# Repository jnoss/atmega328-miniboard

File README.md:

# atmega328-miniboard
This is an atmega328 (arduino compatible) board that uses 3-pin headers (power and ground for each signal pin) enabling the use of very small shields.

See minishields directory for:
- led4pins.sch
- led8pins.sch
- light sensor microshield v3.sch
- rgb_v3.sch
- seg7_minishield.sch
- temp sensor.sch

See [gerber preview image](gerber-previews/mega328_withheaders_andxbee.brd.board-top.png) for a preview of the top layer of atmega328 miniboard

Board preview made using git hooks from [https://github.com/jnoss/eagle-preview-autogen], fork of [https://github.com/tekdemo/eagle-preview-autogen]

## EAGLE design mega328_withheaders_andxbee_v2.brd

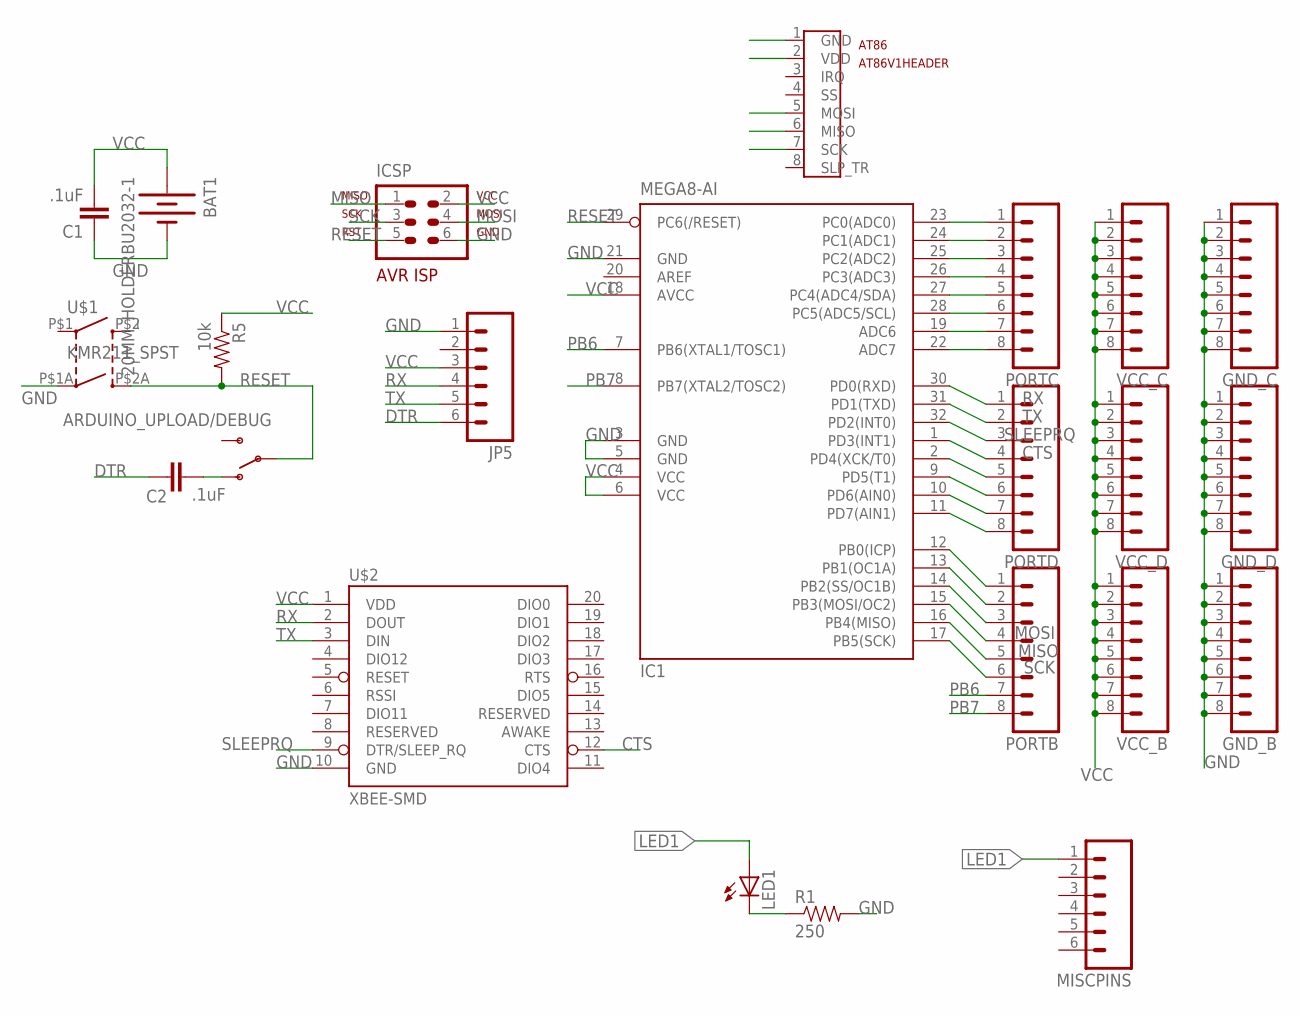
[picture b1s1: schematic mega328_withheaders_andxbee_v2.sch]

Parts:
ARDUINO_UPLOAD/DEBUG: SWITCH-SPDT-SMD-A; SWITCH-SPST-SMD-A
AT86: AT86V1HEADER
BAT1: 20MM_HOLDERBU2032-1; BU2032-1
C1, C2: .1uF; 0603-CAP
GND_B: M081X08; 1X08
GND_C: M081X08; 1X08
GND_D: M081X08; 1X08
IC1: MEGA8-AI; TQFP32-08
ICSP: ISP; AVR-ISP-6
JP5: M06SIP; 1X06
LED1: LEDCHIP-LED0603; CHIP-LED0603
MISCPINS: M06SIP; 1X06
PORTB: M081X08; 1X08
PORTC: M081X08; 1X08
PORTD: M081X08; 1X08
R1: 250; 0603-RES
R5: 10k; 0603-RES
U$1: KMR211_SPST
U$2: XBEE-SMD
VCC_B: M081X08; 1X08
VCC_C: M081X08; 1X08
VCC_D: M081X08; 1X08

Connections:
B0: IC1.12 (PB0(ICP)), PORTB.1
C0: IC1.23 (PC0(ADC0)), PORTC.1
CTS: IC1.1 (PD3(INT1)), PORTD.4, U$2.12 (CTS)
DTR: C2.1, JP5.6
GND: AT86.1 (GND), BAT1.-, C1.1, GND_B.1, GND_B.2, GND_B.3, GND_B.4, GND_B.5, GND_B.6, GND_B.7, GND_B.8, GND_C.1, GND_C.2, GND_C.3, GND_C.4, GND_C.5, GND_C.6, GND_C.7, GND_C.8, GND_D.1, GND_D.2, GND_D.3, GND_D.4, GND_D.5, GND_D.6, GND_D.7, GND_D.8, IC1.3 (GND), IC1.5 (GND), IC1.21 (GND), ICSP.6, JP5.1, R1.2, U$1.P$1A (1B), U$2.10 (GND)
LED1: LED1.A, MISCPINS.1
MISO: AT86.6 (MISO), IC1.16 (PB4(MISO)), ICSP.1, PORTB.5
MOSI: AT86.5 (MOSI), IC1.15 (PB3(MOSI/OC2)), ICSP.4, PORTB.4
unnamed: ARDUINO_UPLOAD/DEBUG.1 (O), C2.2
unnamed: IC1.24 (PC1(ADC1)), PORTC.2
unnamed: IC1.25 (PC2(ADC2)), PORTC.3
unnamed: IC1.26 (PC3(ADC3)), PORTC.4
unnamed: IC1.27 (PC4(ADC4/SDA)), PORTC.5
unnamed: IC1.28 (PC5(ADC5/SCL)), PORTC.6
unnamed: IC1.19 (ADC6), PORTC.7
unnamed: IC1.22 (ADC7), PORTC.8
unnamed: IC1.2 (PD4(XCK/T0)), PORTD.5
unnamed: IC1.9 (PD5(T1)), PORTD.6
unnamed: IC1.10 (PD6(AIN0)), PORTD.7
unnamed: IC1.11 (PD7(AIN1)), PORTD.8
unnamed: IC1.14 (PB2(SS/OC1B)), PORTB.3
unnamed: IC1.13 (PB1(OC1A)), PORTB.2
unnamed: LED1.C, R1.1
PB6: IC1.7 (PB6(XTAL1/TOSC1)), PORTB.7
PB7: IC1.8 (PB7(XTAL2/TOSC2)), PORTB.8
RESET: ARDUINO_UPLOAD/DEBUG.2, IC1.29 (PC6(/RESET)), ICSP.5, R5.2, U$1.P$2A (2B)
RX: IC1.30 (PD0(RXD)), JP5.4, PORTD.1, U$2.2 (DOUT)
SCK: AT86.7 (SCK), IC1.17 (PB5(SCK)), ICSP.3, PORTB.6
SLEEPRQ: IC1.32 (PD2(INT0)), PORTD.3, U$2.9 (DTR/SLEEP_RQ)
TX: IC1.31 (PD1(TXD)), JP5.5, PORTD.2, U$2.3 (DIN)
VCC: AT86.2 (VDD), BAT1.+@1 (+), BAT1.+@2 (+), C1.2, IC1.4 (VCC), IC1.6 (VCC), IC1.18 (AVCC), ICSP.2, JP5.3, R5.1, U$2.1 (VDD), VCC_B.1, VCC_B.2, VCC_B.3, VCC_B.4, VCC_B.5, VCC_B.6, VCC_B.7, VCC_B.8, VCC_C.1, VCC_C.2, VCC_C.3, VCC_C.4, VCC_C.5, VCC_C.6, VCC_C.7, VCC_C.8, VCC_D.1, VCC_D.2, VCC_D.3, VCC_D.4, VCC_D.5, VCC_D.6, VCC_D.7, VCC_D.8

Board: 2 copper layers, 23 parts (1 on the bottom side), 31 nets, no tracks yet.

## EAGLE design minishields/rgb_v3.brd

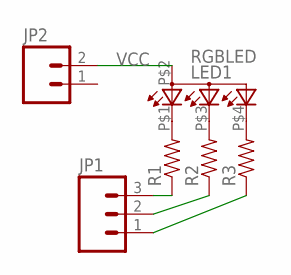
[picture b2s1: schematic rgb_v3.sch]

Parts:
JP1: M03NONPOLAR; 1X03NONPOLAR
JP2: M02PTH; 1X02
LED1: RGBLED; CLVBA-FKA-CAEDH8BBB7A363
R1, R2, R3: RESISTOR0402-RES; 0402-RES

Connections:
unnamed: LED1.P$1 (CRED), R1.2
unnamed: LED1.P$3 (CBLUE), R2.2
unnamed: LED1.P$4 (CGREEN), R3.2
unnamed: JP1.2, R2.1
unnamed: JP1.1, R3.1
unnamed: JP1.3, R1.1
VCC: JP2.2, LED1.P$2 (A)

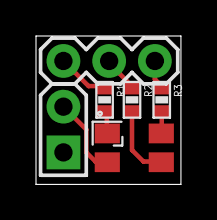
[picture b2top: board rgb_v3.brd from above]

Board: 2 copper layers, 8.1 x 8.2 mm, 6 parts (0 on the bottom side), 7 nets.

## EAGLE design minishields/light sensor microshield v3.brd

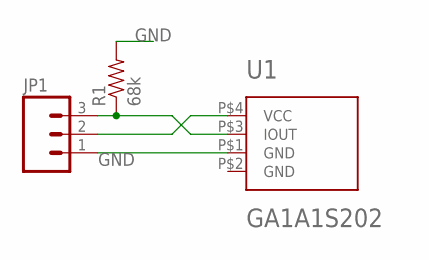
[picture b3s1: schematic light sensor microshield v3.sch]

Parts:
JP1: M03PTH; 1X03
R1: 68k; 0603-RES
U1: GA1A1S202; GA1A12S202

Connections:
GND: JP1.1, R1.2, U1.P$1 (GND), U1.P$2 (GND)
unnamed: JP1.2, U1.P$4 (VCC)
unnamed: JP1.3, R1.1, U1.P$3 (IOUT)

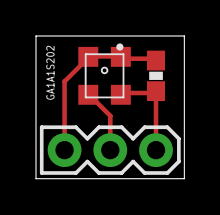
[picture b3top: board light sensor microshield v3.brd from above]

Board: 2 copper layers, 8.2 x 7.9 mm, 3 parts (0 on the bottom side), 3 nets.

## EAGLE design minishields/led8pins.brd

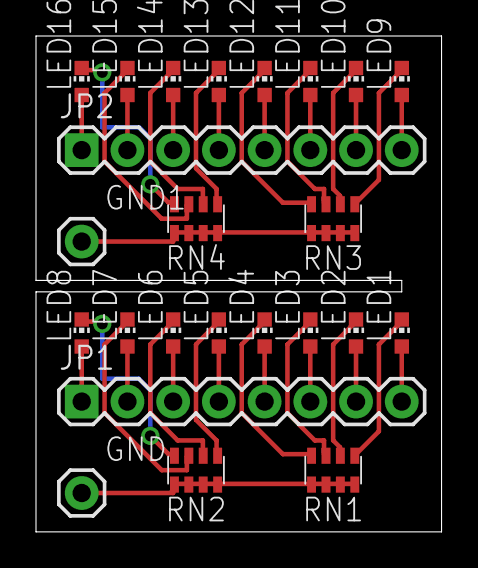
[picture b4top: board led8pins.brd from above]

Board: 2 copper layers, 22.5 x 27.5 mm, 24 parts (0 on the bottom side), 34 nets.

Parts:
GND, GND1: M01PTH; 1X01
JP1, JP2: 1X08
LED1, LED2, LED3, LED4, LED5, LED6, LED7, LED8, LED9, LED10, LED11, LED12, LED13, LED14, LED15, LED16: CHIP-LED0603
RN1, RN2, RN3, RN4: CTS742C083

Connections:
unnamed: JP1.8, LED1.A
unnamed: JP1.7, LED2.A
unnamed: JP1.6, LED3.A
unnamed: JP1.5, LED4.A
unnamed: JP1.4, LED5.A
unnamed: JP1.3, LED6.A
unnamed: JP1.2, LED7.A
unnamed: JP1.1, LED8.A
unnamed: LED1.C, RN1.1
unnamed: LED2.C, RN1.2
unnamed: LED3.C, RN1.3
unnamed: LED4.C, RN1.4
unnamed: LED5.C, RN2.1
unnamed: LED6.C, RN2.2
unnamed: LED7.C, RN2.3
unnamed: LED8.C, RN2.4
unnamed: GND.1, RN1.5, RN1.6, RN1.7, RN1.8, RN2.5, RN2.6, RN2.7, RN2.8
unnamed: JP2.8, LED9.A
unnamed: JP2.7, LED10.A
unnamed: JP2.6, LED11.A
unnamed: JP2.5, LED12.A
unnamed: JP2.4, LED13.A
unnamed: JP2.3, LED14.A
unnamed: JP2.2, LED15.A
unnamed: JP2.1, LED16.A
unnamed: LED9.C, RN3.1
unnamed: LED10.C, RN3.2
unnamed: LED11.C, RN3.3
unnamed: LED12.C, RN3.4
unnamed: LED13.C, RN4.1
unnamed: LED14.C, RN4.2
unnamed: LED15.C, RN4.3
unnamed: LED16.C, RN4.4
unnamed: GND1.1, RN3.5, RN3.6, RN3.7, RN3.8, RN4.5, RN4.6, RN4.7, RN4.8

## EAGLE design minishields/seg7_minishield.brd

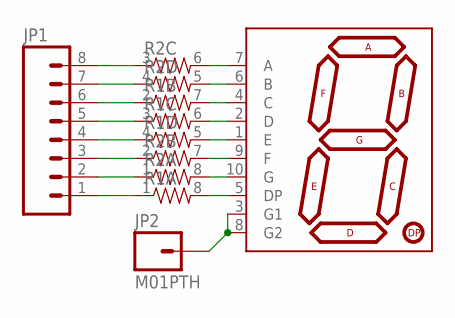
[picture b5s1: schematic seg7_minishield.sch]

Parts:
JP1: M081X08; 1X08
JP2: M01PTH; 1X01
R1, R2: RESISTOR-ARRAY0603-ARV; 0603-ARV
U$1: 7-SEGMENT-DISPLAYPTH; 7-SEGMENT-DISPLAY

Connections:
unnamed: R1.5 (2), U$1.1 (E)
unnamed: R1.6 (2), U$1.2 (D)
unnamed: R1.7 (2), U$1.4 (C)
unnamed: R1.8 (2), U$1.5 (DP)
unnamed: R2.8 (2), U$1.10 (G)
unnamed: R2.7 (2), U$1.9 (F)
unnamed: R2.6 (2), U$1.7 (A)
unnamed: R2.5 (2), U$1.6 (B)
unnamed: JP2.1, U$1.3 (G1), U$1.8 (G2)
unnamed: JP1.1, R1.1
unnamed: JP1.6, R1.2 (1)
unnamed: JP1.5, R1.3 (1)
unnamed: JP1.4, R1.4 (1)
unnamed: JP1.2, R2.1
unnamed: JP1.3, R2.2 (1)
unnamed: JP1.8, R2.3 (1)
unnamed: JP1.7, R2.4 (1)

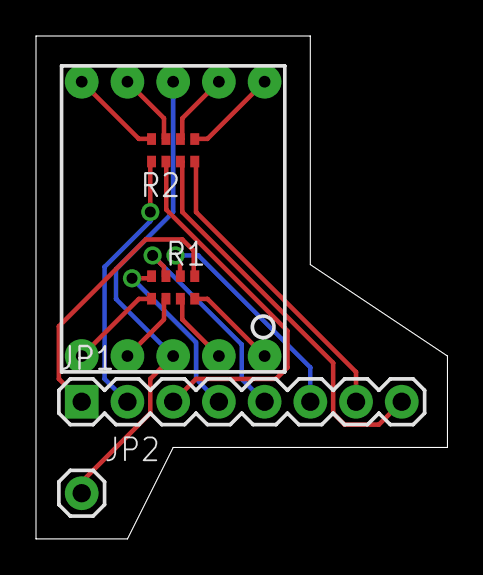
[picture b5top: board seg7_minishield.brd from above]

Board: 2 copper layers, 22.9 x 27.9 mm, 5 parts (0 on the bottom side), 17 nets.

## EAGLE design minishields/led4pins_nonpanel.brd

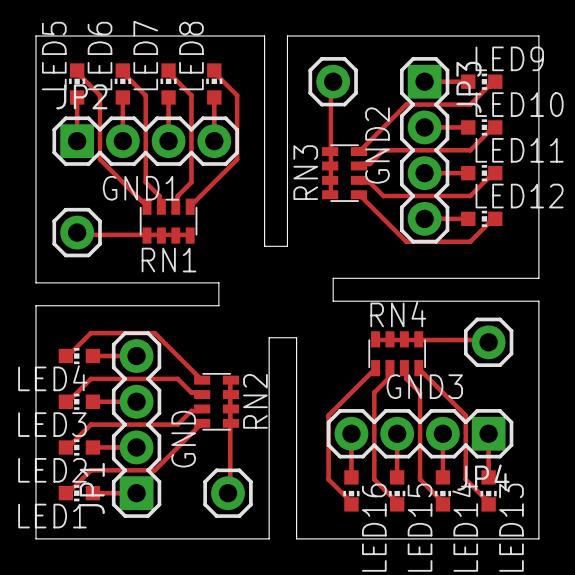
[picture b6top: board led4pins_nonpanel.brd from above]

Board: 2 copper layers, 27.9 x 27.9 mm, 28 parts (0 on the bottom side), 36 nets.

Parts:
GND, GND1, GND2, GND3: M01PTH; 1X01
JP1, JP2, JP3, JP4: 1X04
LED1, LED2, LED3, LED4, LED5, LED6, LED7, LED8, LED9, LED10, LED11, LED12, LED13, LED14, LED15, LED16: CHIP-LED0603
RN1, RN2, RN3, RN4: CTS742C083

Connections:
unnamed: JP1.1, LED1.A
unnamed: JP1.2, LED2.A
unnamed: JP1.3, LED3.A
unnamed: JP1.4, LED4.A
unnamed: JP2.1, LED5.A
unnamed: JP2.2, LED6.A
unnamed: LED1.C, RN2.4
unnamed: LED2.C, RN2.3
unnamed: LED3.C, RN2.2
unnamed: LED4.C, RN2.1
unnamed: JP2.3, LED7.A
unnamed: JP2.4, LED8.A
unnamed: LED5.C, RN1.4
unnamed: LED6.C, RN1.3
unnamed: GND.1, RN2.5, RN2.6, RN2.7, RN2.8
unnamed: LED7.C, RN1.2
unnamed: LED8.C, RN1.1
unnamed: GND1.1, RN1.5, RN1.6, RN1.7, RN1.8
unnamed: JP3.1, LED9.A
unnamed: JP3.2, LED10.A
unnamed: JP3.3, LED11.A
unnamed: JP3.4, LED12.A
unnamed: LED9.C, RN3.4
unnamed: LED10.C, RN3.3
unnamed: LED11.C, RN3.2
unnamed: LED12.C, RN3.1
unnamed: GND2.1, RN3.5, RN3.6, RN3.7, RN3.8
unnamed: JP4.1, LED13.A
unnamed: JP4.2, LED14.A
unnamed: JP4.3, LED15.A
unnamed: JP4.4, LED16.A
unnamed: LED13.C, RN4.4
unnamed: LED14.C, RN4.3
unnamed: LED15.C, RN4.2
unnamed: LED16.C, RN4.1
unnamed: GND3.1, RN4.5, RN4.6, RN4.7, RN4.8

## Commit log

2015-09-24 inital commit
2015-09-24 add minishields
2015-09-24 Update README.md
    add minishields
2015-09-24 add gitignore
2017-02-15 add v2 atmega328 board
    - keying for SVG minishield headers (now SV-G)
    - add at86rf233 header
    - rotate ISP header for easier connection
    - increase font size for labels
2017-02-15 add eagle-preview-autogen
2017-02-15 v2: initial route 4-layer
2017-02-15 v2: initial route 2-layer
2017-02-15 v2: edit labels
2017-02-25 v2: rotate ISP for easier connection
2017-02-25 v2: add switch to enable debugwire
2017-02-25 gitignore .lck
2017-02-25 gitignore vim swap files
2017-02-25 v2: re-rotate isp
2017-02-25 v2: switch battery holder and etc

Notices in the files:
parts and their libraries:
SparkFun-Electromechanical: Licensing: CC v3.0 Share-Alike You are welcome to use this library for commercial purposes.
